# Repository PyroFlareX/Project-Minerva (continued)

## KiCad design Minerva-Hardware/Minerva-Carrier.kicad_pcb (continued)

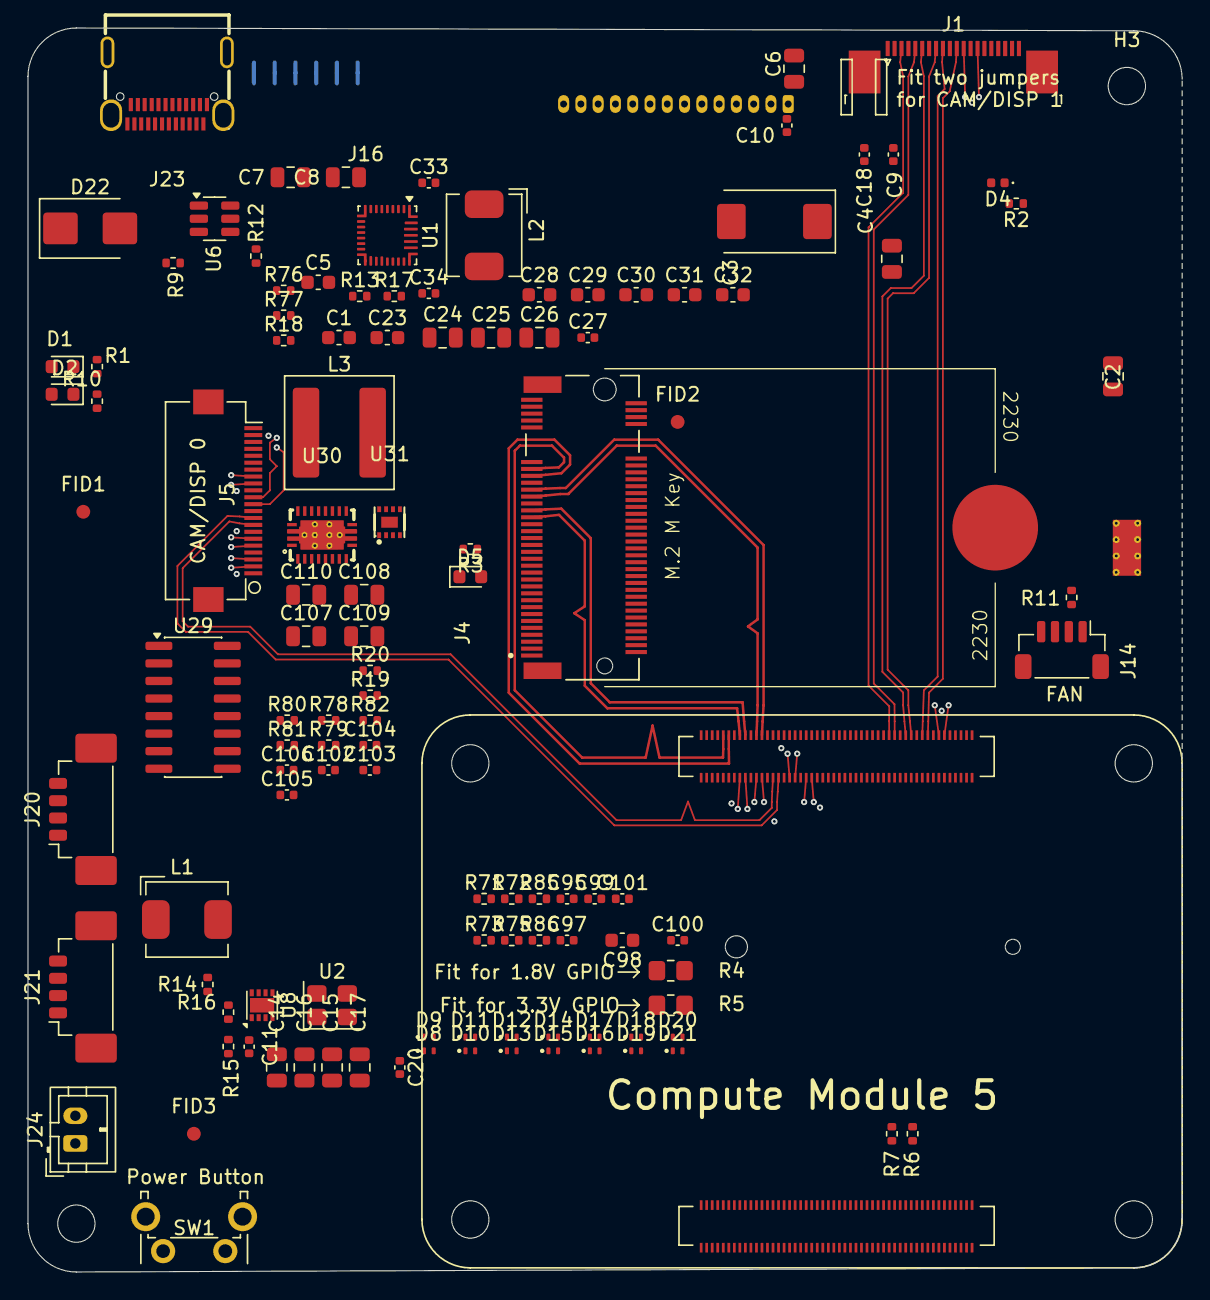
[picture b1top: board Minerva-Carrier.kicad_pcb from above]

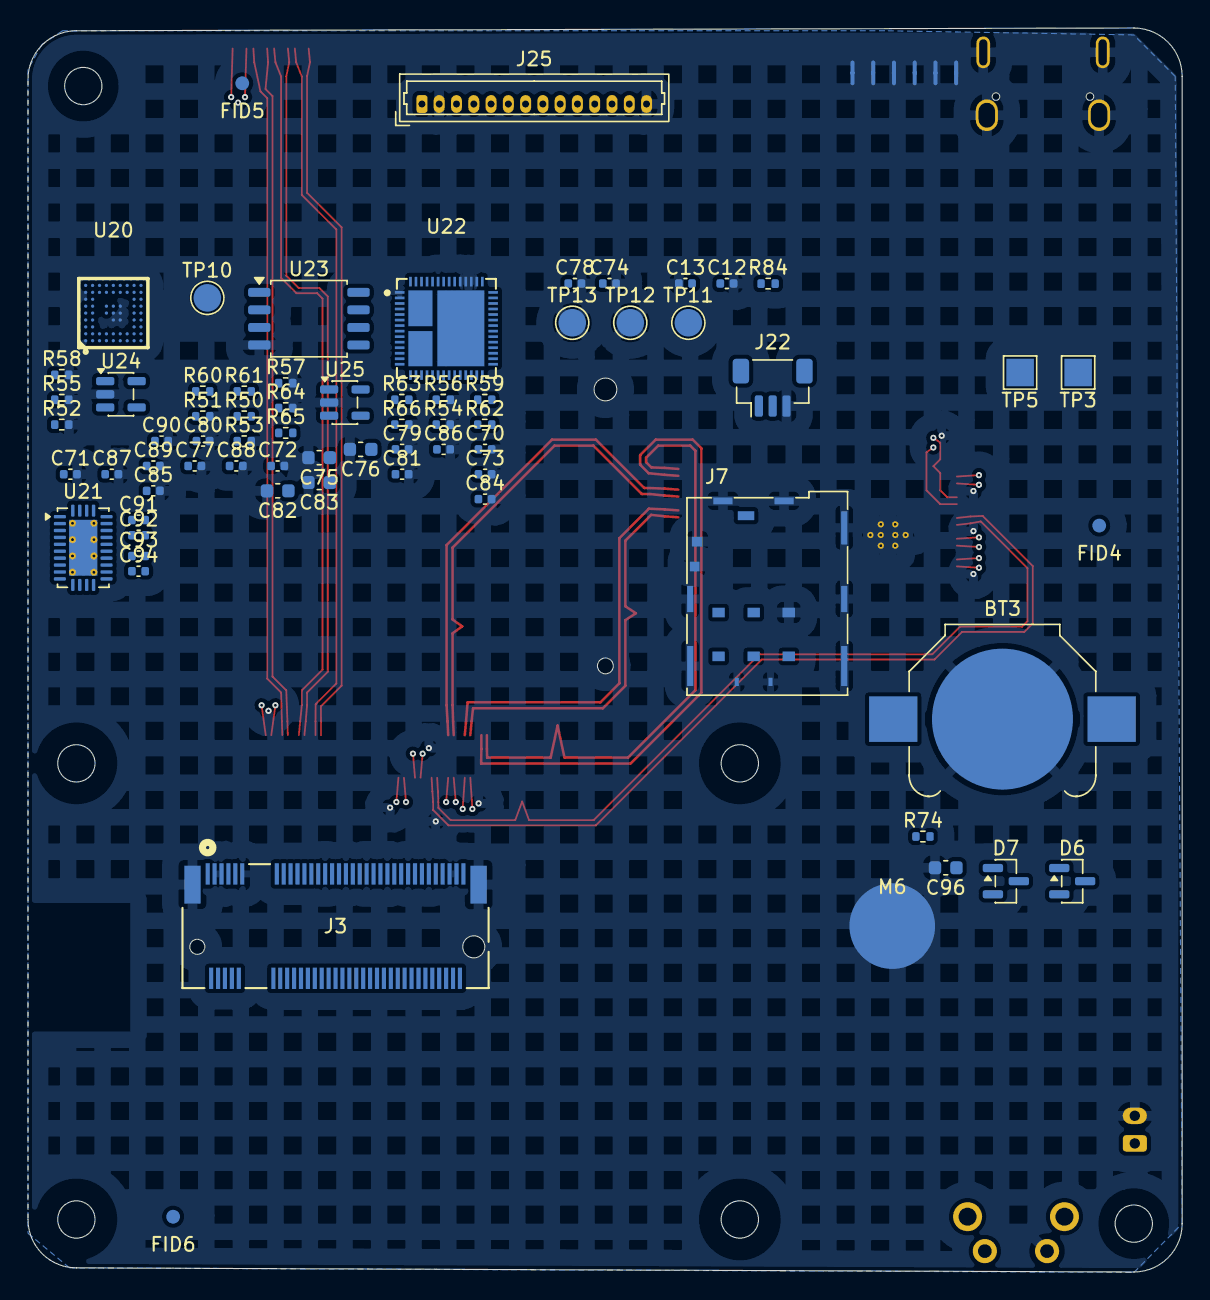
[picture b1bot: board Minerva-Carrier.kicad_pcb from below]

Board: 6 copper layers, 83.5 x 90.0 mm, 190 parts (70 on the bottom side), 179 nets.

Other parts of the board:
FID1, FID2, FID3, FID4, FID5, FID6: Fiducial_1mm_Mask2mm

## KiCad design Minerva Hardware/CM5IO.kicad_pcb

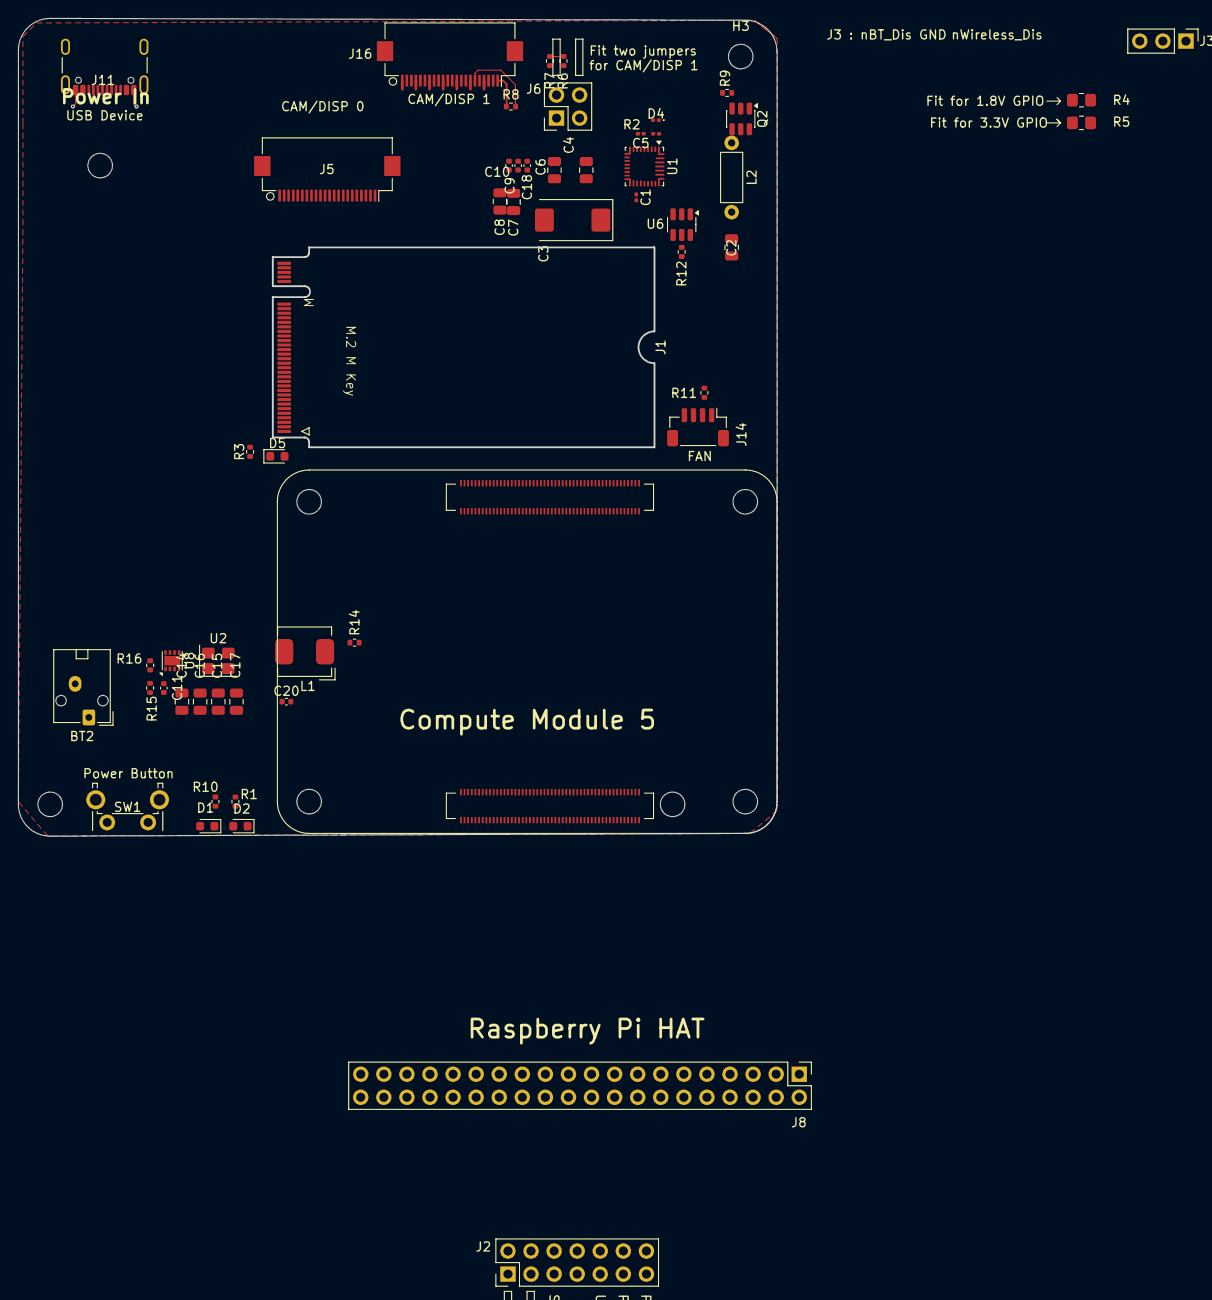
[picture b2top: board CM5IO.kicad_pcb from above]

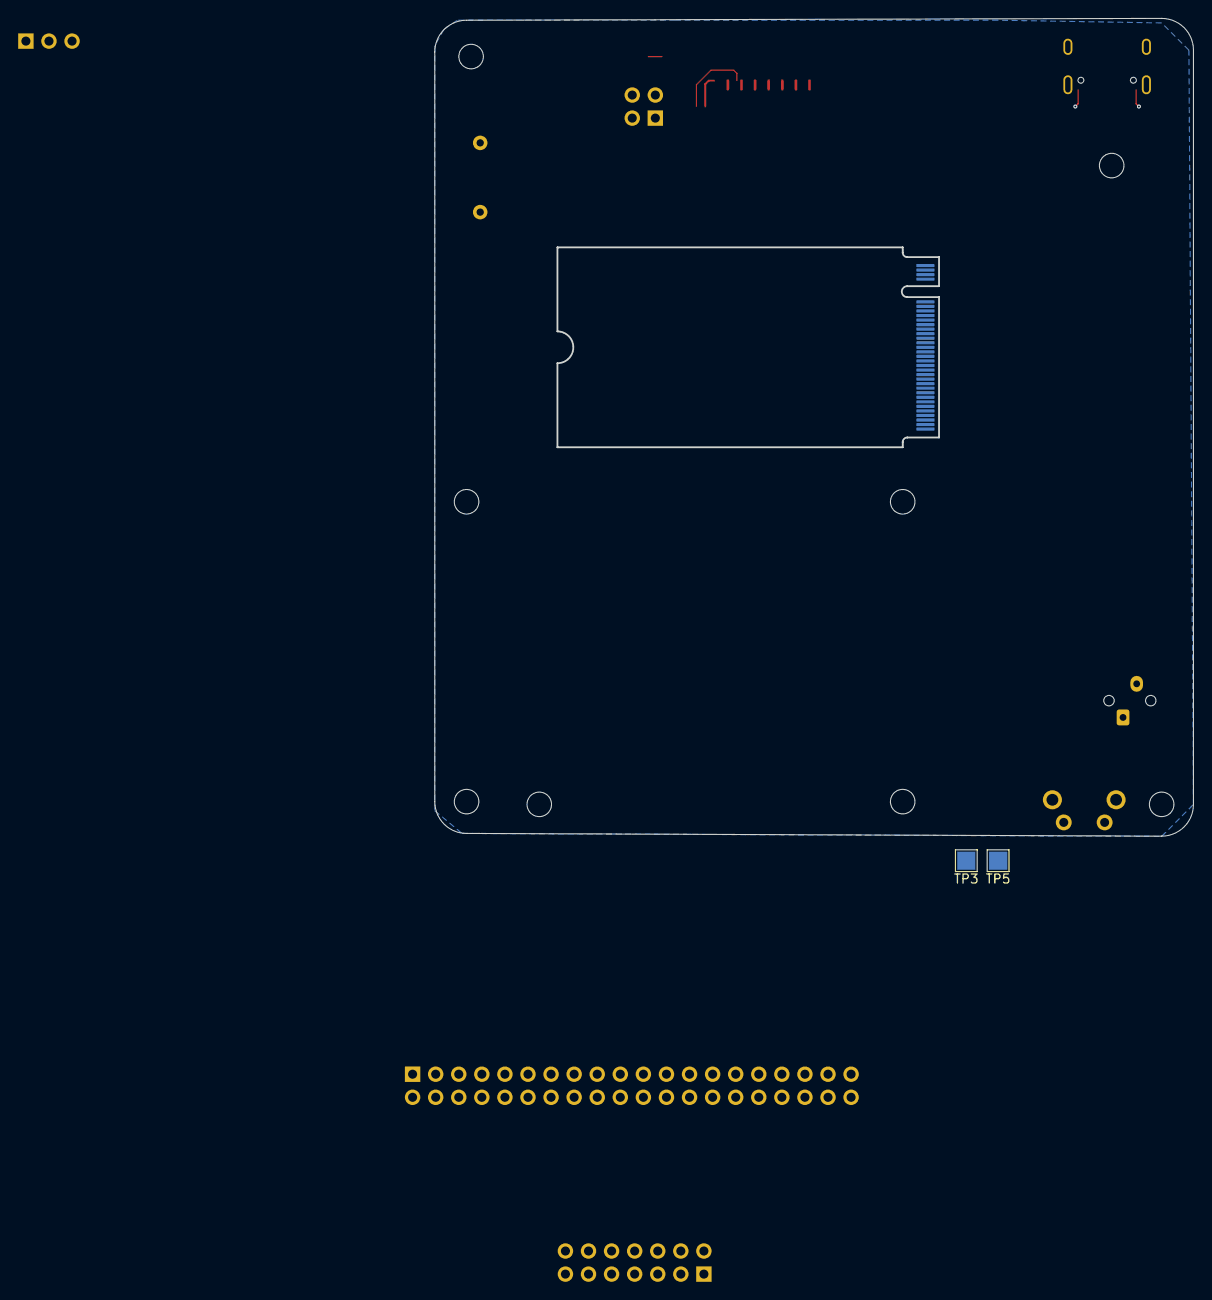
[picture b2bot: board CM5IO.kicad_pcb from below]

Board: 4 copper layers, 83.5 x 90.0 mm, 61 parts (2 on the bottom side), 106 nets.

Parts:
BT2: Battery; JST_ZE_S02B-ZESK-2D_1x02_P1.50mm_Horizontal
C1: C_Small_US; C_0201_0603Metric
C2, C4, C6, C7, C8, C14, C15, C16, C17: 10u; C_0805_2012Metric
C3: 100uF; CP_EIA-7343-31_Kemet-D
C5: 4.7uF 25V; C_0201_0603Metric
C9, C10, C18, C20: 100n; C_0402_1005Metric
C11: 4.7nF; C_0402_1005Metric
D1: LED Red; LED_0603_1608Metric
D2, D5: LED Green; LED_0603_1608Metric
D4: LED; LED_0201_0603Metric
H1, H2, H3, H4: MountingHole; MountingHole_2.7mm_M2.5_DIN965
J1: Bus_M.2_Socket_M; M.2_2242-xx-M
J2: Conn_02x07_Odd_Even; PinHeader_2x07_P2.54mm_Vertical
J3: Conn_01x03; PinHeader_1x03_P2.54mm_Vertical
J5, J16: Conn_01x22_Female; Hirose_FH12-22S-0.5SH_1x22-1MP_P0.50mm_Horizontal
J6: THD-02-R; PinHeader_2x02_P2.54mm_Vertical
J8: THD-20-R; PinHeader_2x20_P2.54mm_Vertical
J11: USB_C_Receptacle_USB2.0; USB_C_Receptacle_GCT_USB4105-xx-A_16P_TopMnt_Horizontal
J14: JST_SHBM04B-SRSS-TB; JST_SH_BM04B-SRSS-TB_1x04-1MP_P1.00mm_Vertical
L1: 2.2uH; L_Bourns_SRP5030CC
L2: 50 nH; L_Axial_L5.3mm_D2.2mm_P7.62mm_Horizontal_Vishay_IM-1
Module1: ComputeModule5-CM5; Raspberry-Pi-5-Compute-Module
Q2: RQ6E080AJ; TSOT-23-6
R1, R3, R10: 1k; R_0402_1005Metric
R2: 10k; R_0201_0603Metric
R4: nf; R_0805_2012Metric_Pad1.20x1.40mm_HandSolder
R5: 0R; R_0805_2012Metric_Pad1.20x1.40mm_HandSolder
R6, R7, R8, R9, R16: 2.2K 1%; R_0402_1005Metric
R11, R15: 10K 1%; R_0402_1005Metric
R12: 15K 1%; R_0402_1005Metric
R14: 100K 1%; R_0402_1005Metric
SW1: Right angle Tact button; SW_Tactile_SPST_Angled_PTS645Vx58-2LFS
TP3, TP5: TestPoint; TestPoint_Pad_2.0x2.0mm
U1: BQ25798; Texas_RQM0029A_VQFN-29_4x4mm_P0.4mm
U2: ASEK-32.768KHZ-L-R-T; Crystal_SMD_3225-4Pin_3.2x2.5mm
U6: AP22653W6; SOT-23-6
U8: AP3441SHE-7B; DFN-8-1EP_2x2mm_P0.5mm_EP1.05x1.75mm

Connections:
/+3.3v: D1.2 (A), D2.2 (A), J5.22, J8.1, J8.17, J16.22, Module1.84 (+3.3v_(Output)), Module1.86 (+3.3v_(Output)), R5.1, R8.1, R11.1
/+5v: C4.1, C6.1, C9.1, C10.1, C18.1, J8.2, J8.4, J14.1, Module1.77 (+5v_(Input)), Module1.79 (+5v_(Input)), Module1.81 (+5v_(Input)), Module1.83 (+5v_(Input)), Module1.85 (+5v_(Input)), Module1.87 (+5v_(Input)), U1.25 (SYS), U8.3 (VIN)
/CC1: J11.A5 (CC1), Module1.94 (CC1)
/CC2: J11.B5 (CC2), Module1.96 (CC2)
/CHARGE_IND_SIG: R2.1, U1.1 (STAT)
/CM5_GPIO/+1.8v: Module1.88 (+1.8v_(Output)), Module1.90 (+1.8v_(Output)), R4.1
/CM5_GPIO/BT_nDis: J3.3, Module1.91 (BT_nDisable)
/CM5_GPIO/CAM_GPIO0: J5.17, Module1.97 (CAM_GPIO0)
/CM5_GPIO/CAM_GPIO1: J5.18, Module1.100 (CAM_GPIO1)
/CM5_GPIO/EEPROM_nWP: J2.4, Module1.20 (EEPROM_nWP)
/CM5_GPIO/GPIO2: J8.3, Module1.58 (GPIO2)
/CM5_GPIO/GPIO3: J8.5, Module1.56 (GPIO3)
/CM5_GPIO/GPIO4: J8.7, Module1.54 (GPIO4)
/CM5_GPIO/GPIO5: J8.29, Module1.34 (GPIO5)
/CM5_GPIO/GPIO6: J8.31, Module1.30 (GPIO6)
/CM5_GPIO/GPIO7: J8.26, Module1.37 (GPIO7)
/CM5_GPIO/GPIO8: J8.24, Module1.39 (GPIO8)
/CM5_GPIO/GPIO9: J8.21, Module1.40 (GPIO9)
/CM5_GPIO/GPIO10: J8.19, Module1.44 (GPIO10)
/CM5_GPIO/GPIO11: J8.23, Module1.38 (GPIO11)
/CM5_GPIO/GPIO12: J8.32, Module1.31 (GPIO12)
/CM5_GPIO/GPIO13: J8.33, Module1.28 (GPIO13)
/CM5_GPIO/GPIO14: J8.8, Module1.55 (GPIO14)
/CM5_GPIO/GPIO15: J8.10, Module1.51 (GPIO15)
/CM5_GPIO/GPIO16: J8.36, Module1.29 (GPIO16)
/CM5_GPIO/GPIO17: J8.11, Module1.50 (GPIO17)
/CM5_GPIO/GPIO18: J8.12, Module1.49 (GPIO18)
/CM5_GPIO/GPIO19: J8.35, Module1.26 (GPIO19)
/CM5_GPIO/GPIO20: J8.38, Module1.27 (GPIO20)
/CM5_GPIO/GPIO21: J8.40, Module1.25 (GPIO21)
/CM5_GPIO/GPIO22: J8.15, Module1.46 (GPIO22)
/CM5_GPIO/GPIO23: J8.16, Module1.47 (GPIO23)
/CM5_GPIO/GPIO24: J8.18, Module1.45 (GPIO24)
/CM5_GPIO/GPIO25: J8.22, Module1.41 (GPIO25)
/CM5_GPIO/GPIO26: J8.37, Module1.24 (GPIO26)
/CM5_GPIO/GPIO27: J8.13, Module1.48 (GPIO27)
/CM5_GPIO/GPIO_VREF: Module1.78 (GPIO_VREF(1.8v/3.3v_Input)), R4.2, R5.2, R6.1, R7.1
/CM5_GPIO/ID_SC: J6.1, J8.28, Module1.35 (ID_SC)
/CM5_GPIO/ID_SD: J6.3, J8.27, Module1.36 (ID_SD)
/CM5_GPIO/PMIC_ENABLE: J2.12, Module1.99 (PMIC_ENABLE)
/CM5_GPIO/PWM: J14.2, Module1.19 (FAN_PWM), R11.2
/CM5_GPIO/PWR_BUT: J2.14, Module1.92 (PWR_BUT), SW1.1
/CM5_GPIO/TACHO: J14.4, Module1.16 (FAN_TACHO)
/CM5_GPIO/USBOTG: J2.10, Module1.101 (USB_OTG_ID)
/CM5_GPIO/WL_nDis: J3.1, Module1.89 (WiFi_nDisable)
/CM5_GPIO/nPWR_LED: Module1.95 (LED_nPWR), R10.2
/CM5_GPIO/nRPIBOOT: J2.2, Module1.93 (nRPIBOOT)
/CM5_HighSpeed/+5v: C2.1, U6.1 (IN)
/CM5_HighSpeed/DPHY0_C_N: J5.8, Module1.127 (MIPI0_C_N)
/CM5_HighSpeed/DPHY0_C_P: J5.9, Module1.129 (MIPI0_C_P)
/CM5_HighSpeed/DPHY0_D0_N: J5.2, Module1.115 (MIPI0_D0_N)
/CM5_HighSpeed/DPHY0_D0_P: J5.3, Module1.117 (MIPI0_D0_P)
/CM5_HighSpeed/DPHY0_D1_N: J5.5, Module1.121 (MIPI0_D1_N)
/CM5_HighSpeed/DPHY0_D1_P: J5.6, Module1.123 (MIPI0_D1_P)
/CM5_HighSpeed/DPHY0_D2_N: J5.11, Module1.133 (MIPI0_D2_N)
/CM5_HighSpeed/DPHY0_D2_P: J5.12, Module1.135 (MIPI0_D2_P)
/CM5_HighSpeed/DPHY0_D3_N: J5.14, Module1.139 (MIPI0_D3_N)
/CM5_HighSpeed/DPHY0_D3_P: J5.15, Module1.141 (MIPI0_D3_P)
/CM5_HighSpeed/DPHY1_C_N: J16.8, Module1.187 (MIPI1_C_N)
/CM5_HighSpeed/DPHY1_C_P: J16.9, Module1.189 (MIPI1_C_P)
/CM5_HighSpeed/DPHY1_D0_N: J16.2, Module1.175 (MIPI1_D0_N)
/CM5_HighSpeed/DPHY1_D0_P: J16.3, Module1.177 (MIPI1_D0_P)
/CM5_HighSpeed/DPHY1_D1_N: J16.5, Module1.181 (MIPI1_D1_N)
/CM5_HighSpeed/DPHY1_D1_P: J16.6, Module1.183 (MIPI1_D1_P)
/CM5_HighSpeed/DPHY1_D2_N: J16.11, Module1.193 (MIPI1_D2_N)
/CM5_HighSpeed/DPHY1_D2_P: J16.12, Module1.195 (MIPI1_D2_P)
/CM5_HighSpeed/DPHY1_D3_N: J16.14, Module1.194 (MIPI1_D3_N)
/CM5_HighSpeed/DPHY1_D3_P: J16.15, Module1.196 (MIPI1_D3_P)
/CM5_HighSpeed/PCIE_CLK_N: J1.53 (REFCLKn), Module1.112 (PCIe_CLK_N)
/CM5_HighSpeed/PCIE_CLK_P: J1.55 (REFCLKp), Module1.110 (PCIe_CLK_P)
/CM5_HighSpeed/PCIE_PWR_EN: Module1.106 (PCIE_PWR_EN), R14.1, U8.7 (EN)
/CM5_HighSpeed/PCIE_RX_N: J1.43 (PERp0/SATA-B-), Module1.118 (PCIe_RX_N)
/CM5_HighSpeed/PCIE_RX_P: J1.41 (PERn0/SATA-B+), Module1.116 (PCIe_RX_P)
/CM5_HighSpeed/PCIE_TX_N: J1.49 (PETp0/SATA-A+), Module1.124 (PCIe_TX_N)
/CM5_HighSpeed/PCIE_TX_P: J1.47 (PETn0/SATA-A-), Module1.122 (PCIe_TX_P)
/CM5_HighSpeed/PCIE_nCLKREQ: J1.52 (~CLKREQ), Module1.102 (PCIe_nCLKREQ)
/CM5_HighSpeed/PCIE_nRST: J1.50 (~PERST), Module1.109 (PCIe_nRST)
/CM5_HighSpeed/PCIE_nWAKE: J1.54 (~PEWAKE), Module1.104 (PCIE_nWAKE)
/CM5_HighSpeed/SCL0: J5.20, Module1.80 (SCL0)
/CM5_HighSpeed/SCL1: J6.2, J16.20, R7.2
/CM5_HighSpeed/SDA0: J5.21, Module1.82 (SDA0)
/CM5_HighSpeed/SDA1: J6.4, J16.21, R6.2
/CM5_HighSpeed/VBUS: C3.1, C7.1, C8.1, U6.6 (OUT)
/CM5_HighSpeed/VBUS_EN: Module1.111 (VBUS_EN), U6.3 (EN)
/PCIe-M2/FB: C11.2, R15.2, R16.1, U8.1 (FB)
/PCIe-M2/M2_3v3: C11.1, C14.1, C15.1, C16.1, C17.1, C20.1, D5.2 (A), J1.2 (3.3V), J1.4 (3.3V), J1.12 (3.3V), J1.14 (3.3V), J1.16 (3.3V), J1.18 (3.3V), J1.70 (3.3V), J1.72 (3.3V), J1.74 (3.3V), L1.2, R15.1, U2.1 (EN), U2.4 (VDD)
/USB2_N: J11.A7 (D-), J11.B7 (D-), Module1.103 (USB2_N)
/USB2_P: J11.A6 (D+), J11.B6 (D+), Module1.105 (USB2_P)
/VBUS: J11.A4 (VBUS), J11.A9 (VBUS), J11.B4 (VBUS), J11.B9 (VBUS), Q2.3 (G), R9.1
GND: BT2.2 (-), C1.2, C2.2, C3.2, C4.2, C5.2, C6.2, C7.2, C8.2, C9.2, C10.2, C14.2, C15.2, C16.2, C17.2, C18.2, C20.2, D4.1 (K), J1.1 (GND), J1.3 (GND), J1.9 (GND), J1.15 (GND), J1.21 (GND), J1.27 (GND), J1.33 (GND), J1.39 (GND), J1.45 (GND), J1.51 (GND), J1.57 (GND), J1.71 (GND), J1.73 (GND), J1.75 (GND), J2.1, J2.3, J2.5, J2.7, J2.9, J2.11, J2.13, J3.2, J5.1, J5.4, J5.7, J5.10, J5.13, J5.16, J5.19, J8.6, J8.9, J8.14, J8.20, J8.25, J8.30, J8.34, J8.39, J11.A1 (GND), J11.A12 (GND), J11.B1 (GND), J11.B12 (GND), J11.S1 (SHIELD), J14.3, J16.1, J16.4, J16.7, J16.10, J16.13, J16.16, J16.19, Module1.1 (GND), Module1.2 (GND), Module1.7 (GND), Module1.8 (GND), Module1.13 (GND), Module1.14 (GND), Module1.22 (GND), Module1.23 (GND), Module1.32 (GND), Module1.33 (GND), Module1.42 (GND), Module1.43 (GND), Module1.52 (GND), Module1.53 (GND), Module1.59 (GND), Module1.60 (GND), Module1.65 (GND), Module1.66 (GND), Module1.71 (GND), Module1.74 (GND), Module1.98 (GND), Module1.107 (GND), Module1.108 (GND), Module1.113 (GND), Module1.114 (GND), Module1.119 (GND), Module1.120 (GND), Module1.125 (GND), Module1.126 (GND), Module1.131 (GND), Module1.132 (GND), Module1.137 (GND), Module1.138 (GND), Module1.144 (GND), Module1.150 (GND), Module1.155 (GND), Module1.156 (GND), Module1.161 (GND), Module1.162 (GND), Module1.167 (GND), Module1.168 (GND), Module1.173 (GND), Module1.174 (GND), Module1.179 (GND), Module1.180 (GND), Module1.185 (GND), Module1.186 (GND), Module1.191 (GND), Module1.192 (GND), Module1.197 (GND), Module1.198 (GND), R9.2, R12.2, R14.2, R16.2, SW1.2, U1.27 (GND), U2.2 (GND), U6.2 (GND), U8.4 (PGND), U8.8 (SGND), U8.9 (PAD)
unnamed: BT2.1 (+), C1.1, U1.18 (BATP), U1.22 (BAT), U1.23 (BAT)
unnamed: D1.1 (K), R10.1, TP5.1
unnamed: D2.1 (K), R1.1, TP3.1
unnamed: D4.2 (A), R2.2
unnamed: D5.1 (K), R3.1
unnamed: J1.10 (DAS/~DSS/~LED1), R3.2
unnamed: J1.68 (SUSCLK), U2.3 (Out)
unnamed: J16.17, R8.2
unnamed: Module1.21 (LED_nACT), R1.2
unnamed: Q2.4 (S), U1.2 (VBUS), U1.3 (VBUS)
unnamed: Q2.1 (D), Q2.2 (D), Q2.5 (D), Q2.6 (D), U1.11 (ACDRV1)
unnamed: C5.1, U1.5 (REGN)
unnamed: L2.1, U1.28 (SW1)
unnamed: L2.2, U1.26 (SW2)
unnamed: R12.1, U6.5 (ILIM)
unnamed: L1.1, U8.6 (LX)

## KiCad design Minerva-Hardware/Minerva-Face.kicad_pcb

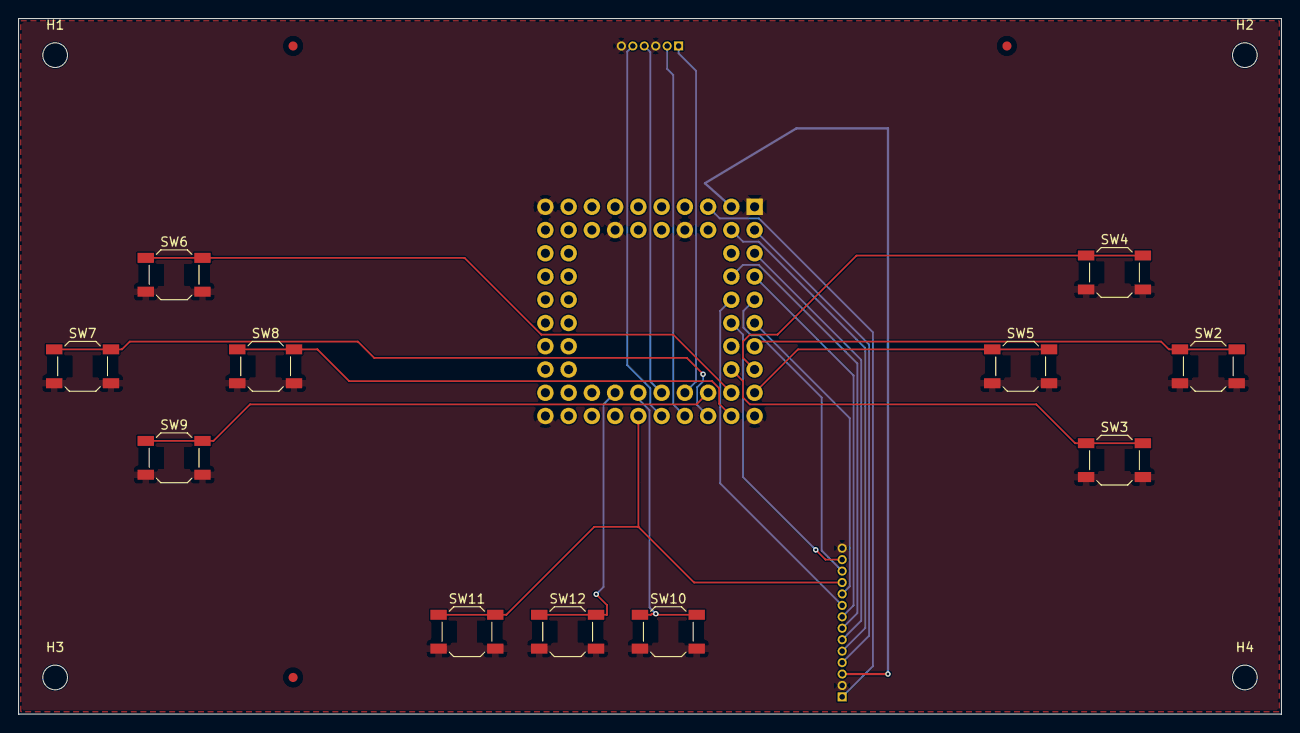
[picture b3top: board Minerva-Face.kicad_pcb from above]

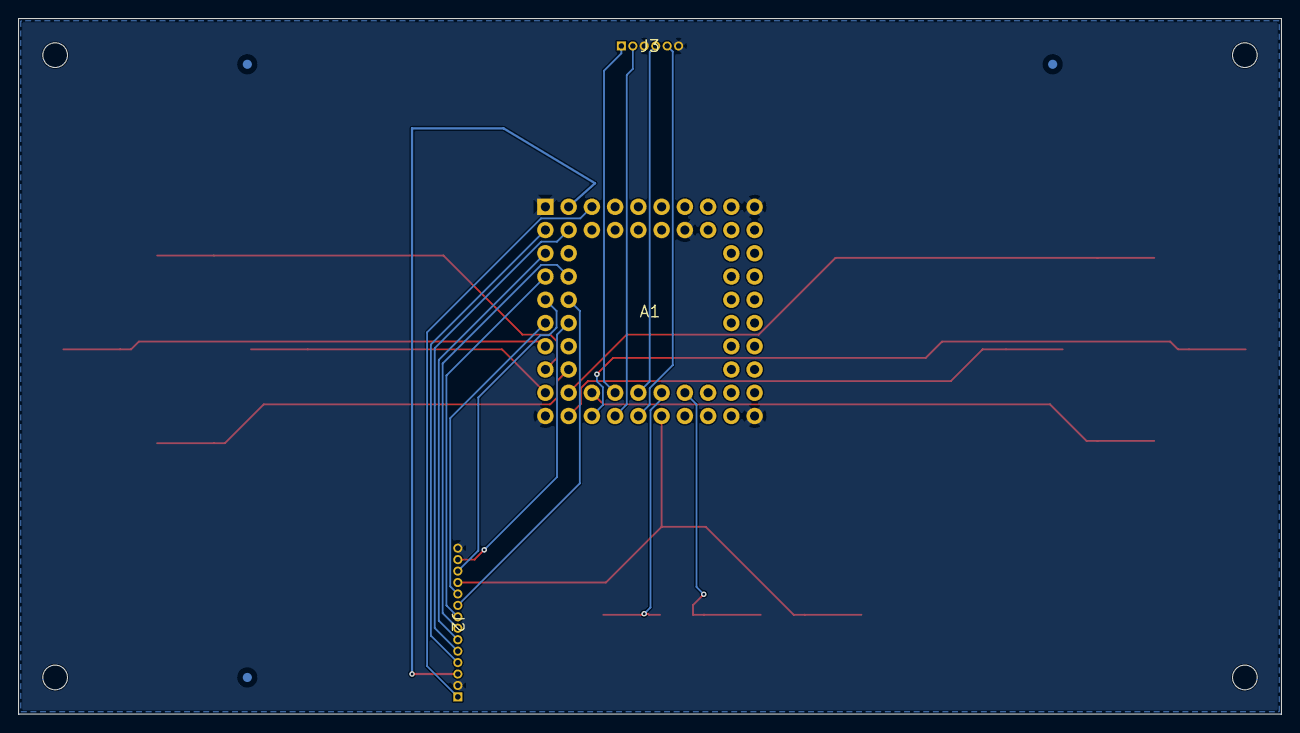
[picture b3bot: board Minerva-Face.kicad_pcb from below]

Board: 2 copper layers, 138.0 x 76.0 mm, 24 parts (6 on the bottom side), 27 nets.

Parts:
A1: Core2350B0; Core2350B_stamp64
FID1, FID2, FID3, FID4, FID5, FID6: Fiducial_1mm_Mask2mm
H1, H2, H3, H4: MountingHole_2.7mm_M2.5_DIN965
J2: PicoBlade 14P; Molex_PicoBlade_53047-1410_1x14_P1.25mm_Vertical
J3: PicoBlade 6P; Molex_PicoBlade_53047-0610_1x06_P1.25mm_Vertical
SW2, SW3, SW4, SW5, SW6, SW7, SW8, SW9, SW10, SW11, SW12: SW_SPST_SKQG_WithStem

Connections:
/+5V: A1.31, J2.1
/AMP_nMUTE: A1.9, J2.12
/AMP_nSD: A1.12, J2.13
/BQ_SCL: A1.10, J2.9
/BQ_SDA: A1.7, J2.8
/BUT_A: A1.13, SW2.1
/BUT_B: A1.16, SW3.1
/BUT_DOWN: A1.38, SW9.1
/BUT_HOME: A1.46, SW12.1
/BUT_L: A1.40, J3.1
/BUT_LEFT: A1.37, SW7.1
/BUT_R: A1.42, J3.4
/BUT_RIGHT: A1.35, SW8.1
/BUT_START: A1.44, SW10.1
/BUT_UP: A1.36, SW6.1
/BUT_X: A1.15, SW4.1
/BUT_Y: A1.34, SW5.1
/BUT_ZL: A1.39, J3.2
/BUT_ZR: A1.41, J3.5
/PD_I2C_IRQ: A1.3, J2.5
/PD_I2C_SCL: A1.4, J2.4
/PD_I2C_SDA: A1.2, J2.3
/PWR_BUT: A1.11, J2.10
/SCL_I2C: A1.8, J2.7
/SDA_I2C: A1.5, J2.6
/nRPIBOOT: A1.43, J2.11, SW11.1
GND: A1.1, A1.17, A1.24, A1.30, A1.33, A1.49, J2.2, J2.14, J3.3, J3.6, SW2.2, SW3.2, SW4.2, SW5.2, SW6.2, SW7.2, SW8.2, SW9.2, SW10.2, SW11.2, SW12.2

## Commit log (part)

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2026-03-28 Claude working
2026-03-28 Update ignore and markdown description
2026-03-29 Good progress make and emulator screen runs
2026-03-29 Fixing up more ui before next vibe code sesh
2026-03-29 Implementing some configs
2026-03-30 Building apps phase one
2026-03-30 PHase 2 claude
2026-04-05 Trying to fix input
2026-04-05 Some vibe coding testing for running it over a websocket
2026-04-06 Setting up building on CM5
2026-04-06 wip vnc fix
2026-04-06 VNC works!
2026-04-06 Works except for dpad and the stick navigation
2026-04-08 try to improve build times
2026-04-09 Fix the kicad file git tracking and work on the PCB board
2026-04-13 Rename and commit actions due to mishap of location naming/saving
2026-04-14 renames
2026-04-19 Adding MiniPCI-E stuff
2026-04-22 Update KiCad and start working on the faceplate pcb
2026-04-24 Adding in the M.2 B WWAN
2026-04-24 Some scripts
2026-05-11 Redid the BQ powerpath unit
2026-05-19 working on pcb more
2026-05-20 Nu torchform.
2026-05-21 wip torchform
2026-05-28 wip shit
2026-06-05 need to improve diff pair routing
2026-06-06 Make my github better and show some of what i'm working on
